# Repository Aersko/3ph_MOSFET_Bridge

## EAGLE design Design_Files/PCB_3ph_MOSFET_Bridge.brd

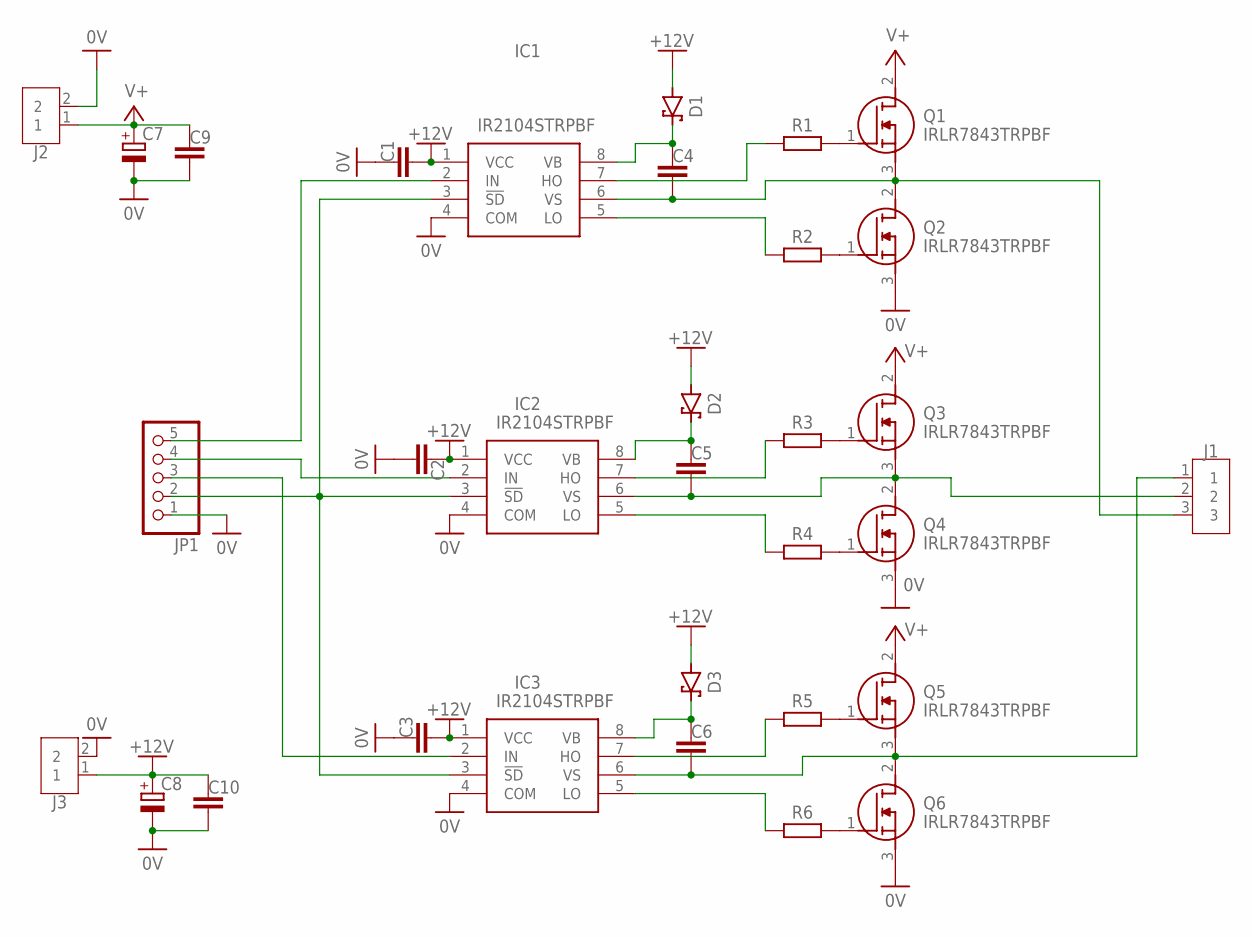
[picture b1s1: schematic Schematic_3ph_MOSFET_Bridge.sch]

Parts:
C1, C2, C3, C4, C5, C6, C9, C10: CAPACITOR_CHIP-0805(2012-METRIC); CAPC2012X110
C7: C-POL_RADIAL-11MM-DIA; CAPPRD508W65D1000H1100B
C8: C-POL_TANTALUM-2412(6032-METRIC); CAPMP6032X280N
D1, D2, D3: MBR0520LT1G; SODFL3718X115
IC1, IC2, IC3: IR2104STRPBF; SOIC127P600X175-8N
J1: TERM-BLK-3P; TERMBLK_508-3N
J2, J3: TERM-BLK-2P; TERMBLK_508-2N
JP1: PINHD-1X5; 1X05
Q1, Q2, Q3, Q4, Q5, Q6: IRLR7843TRPBF
R1, R2, R3, R4, R5, R6: RESISTOR__CHIP-0805(2012-METRIC); RESC2012X65

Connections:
0V: C1.1, C2.2, C3.1, C7.2 (-), C8.2 (-), C9.2, C10.2, IC1.4 (COM), IC2.4 (COM), IC3.4 (COM), J2.2, J3.2, JP1.1, Q2.3 (S), Q4.3 (S), Q6.3 (S)
+12V: C1.2, C2.1, C3.2, C8.1 (+), C10.1, D1.2 (A), D2.2 (A), D3.2 (A), IC1.1 (VCC), IC2.1 (VCC), IC3.1 (VCC), J3.1
unnamed: C4.2, IC1.6 (VS), J1.3, Q1.3 (S), Q2.2 (D)
unnamed: C5.2, IC2.6 (VS), J1.2, Q3.3 (S), Q4.2 (D)
unnamed: C6.2, IC3.6 (VS), J1.1, Q5.3 (S), Q6.2 (D)
unnamed: Q1.1 (G), R1.2
unnamed: Q2.1 (G), R2.2
unnamed: Q3.1 (G), R3.2
unnamed: Q4.1 (G), R4.2
unnamed: Q5.1 (G), R5.2
unnamed: Q6.1 (G), R6.2
unnamed: IC1.7 (HO), R1.1
unnamed: IC1.5 (LO), R2.1
unnamed: IC2.7 (HO), R3.1
unnamed: IC2.5 (LO), R4.1
unnamed: IC3.7 (HO), R5.1
unnamed: IC3.5 (LO), R6.1
unnamed: IC1.3 (!SD), IC2.3 (!SD), IC3.3 (!SD), JP1.2
unnamed: IC1.2 (IN), JP1.5
unnamed: IC2.2 (IN), JP1.4
unnamed: IC3.2 (IN), JP1.3
unnamed: C4.1, D1.1 (C), IC1.8 (VB)
unnamed: C5.1, D2.1 (C), IC2.8 (VB)
unnamed: C6.1, D3.1 (C), IC3.8 (VB)
V+: C7.1 (+), C9.1, J2.1, Q1.2 (D), Q3.2 (D), Q5.2 (D)

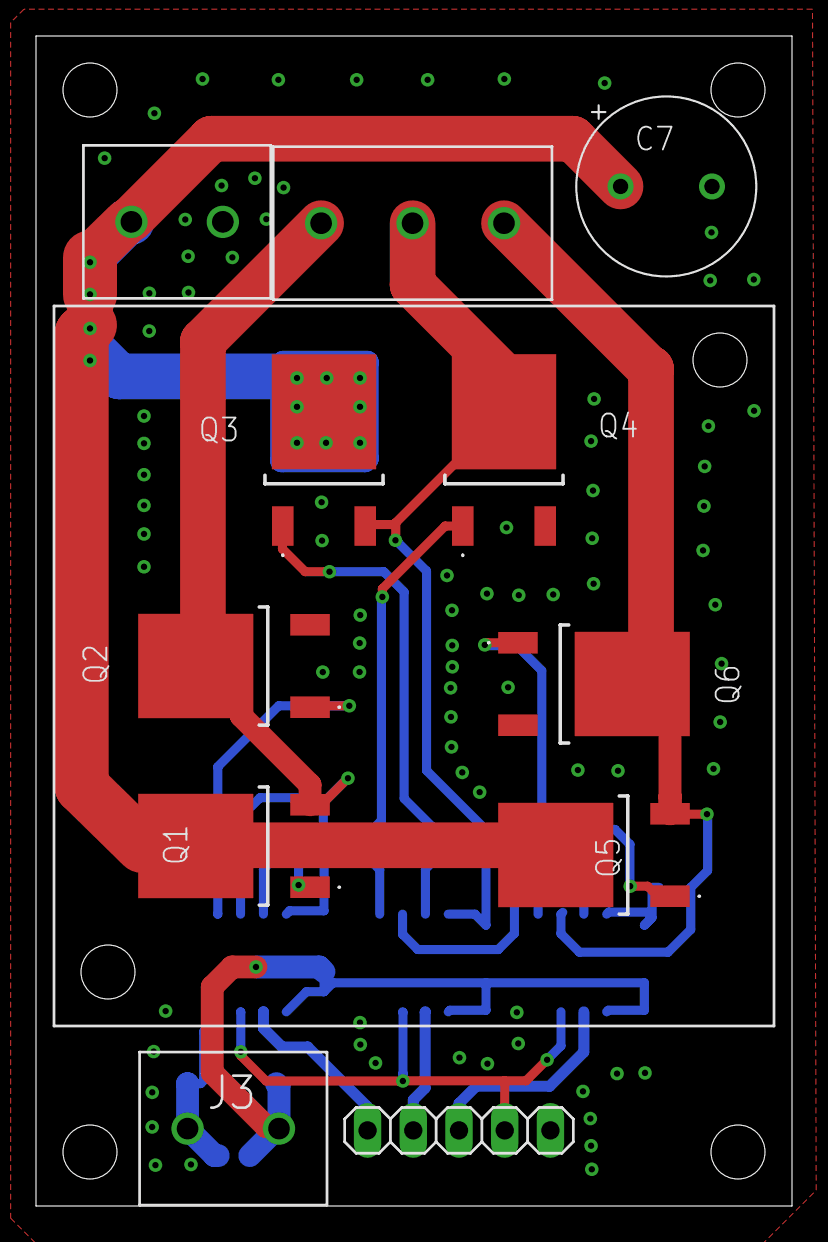
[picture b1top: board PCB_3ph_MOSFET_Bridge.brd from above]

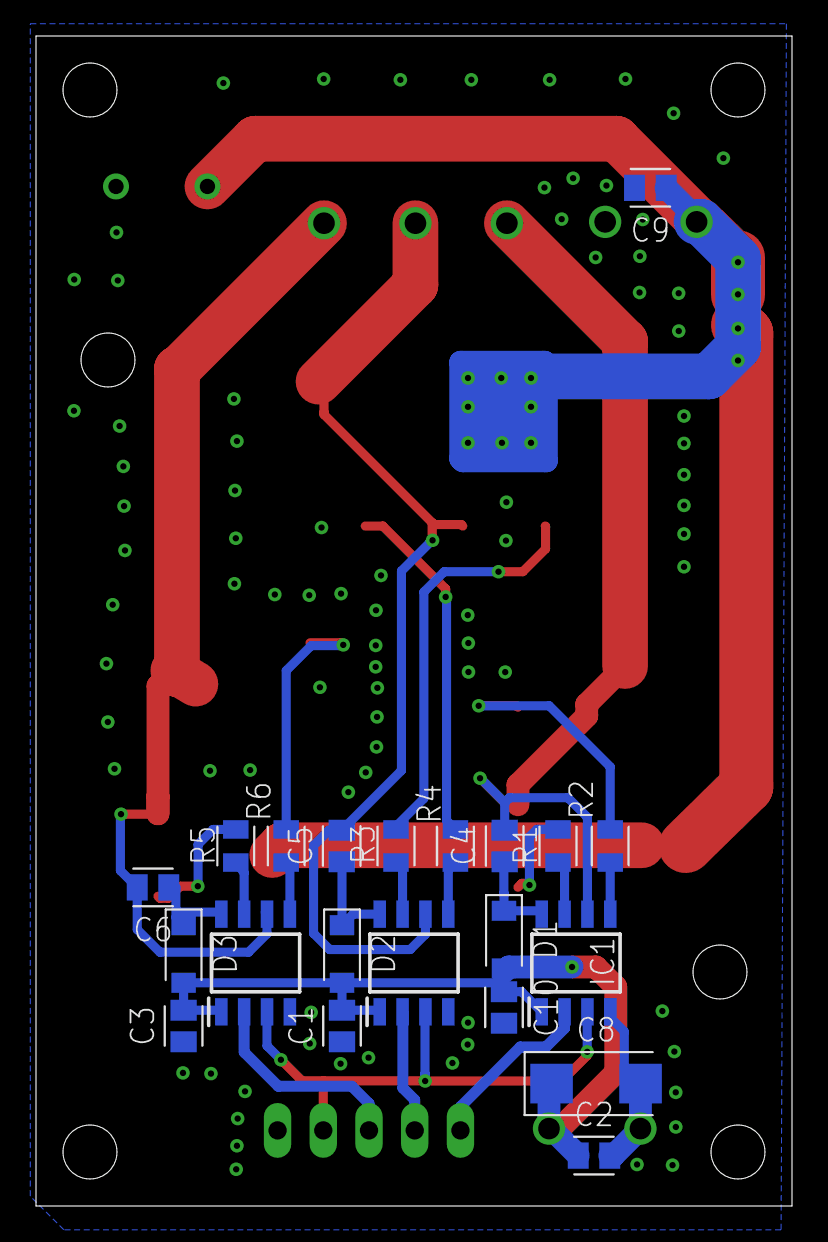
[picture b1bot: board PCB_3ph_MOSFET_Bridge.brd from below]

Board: 2 copper layers, 42.0 x 65.0 mm, 32 parts (21 on the bottom side), 25 nets.

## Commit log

2025-08-09 Add files via upload
    BOM file holds:
    6 IRLR7843TRPBF MOSFET
    3 IR2104S Driver
    1 282837-3 Connector (3phase output)
    1 282837-2 Connector (60V DC Power IN)
    6 0805(2012 metric) R1...R6 62-510 Ohm gate driver Resistor see the driver and MOSFET datasheet for this parameter.
2025-08-09 LICENSE
